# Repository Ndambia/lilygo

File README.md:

# LilyGo IoT Multi-Function PCB

A custom 4-layer KiCad PCB design integrating an ESP32 Wi-Fi/Bluetooth microcontroller with a SIM7600G-H 4G LTE Cat-4 cellular module, comprehensive power management, GPS tracking, GPRS connectivity, USB-C charging, LiPo battery management, environmental sensing, and USB-to-UART programming support.

---

## Table of Contents

- [Overview](#overview)
- [PCB Preview](#pcb-preview)
- [Schematic Overview](#schematic-overview)
- [Key Features](#key-features)
- [System Architecture](#system-architecture)
- [Schematic Sheets](#schematic-sheets)
- [Bill of Materials Summary](#bill-of-materials-summary)
- [Power System](#power-system)
- [Connectivity](#connectivity)
- [PCB Stackup & Design Rules](#pcb-stackup--design-rules)
- [Gerber & Manufacturing Files](#gerber--manufacturing-files)
- [Custom Libraries](#custom-libraries)
- [Datasheets](#datasheets)
- [Repository Structure](#repository-structure)
- [Getting Started](#getting-started)

---

## Overview

This project is a compact, feature-rich IoT development board built around the **ESP32-WROOM-32** and the **SIM7600G-H R2** 4G LTE module. It is designed for applications requiring cellular connectivity (4G/GPRS), GPS positioning, local Wi-Fi/Bluetooth, environmental sensing, and flexible power management from USB-C or a LiPo battery.

The board is designed in **KiCad** and targets JLCPCB / LCSC manufacturing and assembly (full BOM with LCSC part numbers included).

---

## PCB Preview

### Front Side (3D Render)

### Back Side (3D Render)

### PCB Layout (Top View)

---

## Schematic Overview

The full schematic (all sheets combined) is available as:

- 📄 [`PCB info/schematic.pdf`](PCB%20info/schematic.pdf) — Full combined schematic (all sheets)

Individual sheet PDFs:

| Sheet | Description | PDF |
|---|---|---|
| Root | Top-level schematic, ESP32, USB-UART, interfaces | *(see full schematic)* |
| BUCK\_CONVERTER\_3V3\_2A | 3.3 V / 2 A step-down (TPS56339DDCR) | [`schematic-BUCK_CONVERTER_3V3_2A_TPS56339DDCR.pdf`](PCB%20info/schematic-BUCK_CONVERTER_3V3_2A_TPS56339DDCR.pdf) |
| LIPO\_BAT\_CHARGER\_TP4056 | LiPo charger and protection circuit | [`schematic-LIPO_BAT_CHARGER_TP4056.pdf`](PCB%20info/schematic-LIPO_BAT_CHARGER_TP4056.pdf) |
| MT3608\_5V\_BOOST\_CONVERTOR | 5 V boost converter (MT3608) | [`schematic-MT3608_5V_BOOST_CONVERTOR.pdf`](PCB%20info/schematic-MT3608_5V_BOOST_CONVERTOR.pdf) |
| POWER\_PATH\_SELECTOR | Automatic USB/Battery power path switching | [`schematic-POWER_PATH_SELECTOR.pdf`](PCB%20info/schematic-POWER_PATH_SELECTOR.pdf) |
| SIM808\_GPRS\_GPS\_MODULE | SIM7600G-H R2 4G/GPS module and support circuitry | [`schematic-SIM808_GPRS_GPS_MODULE.pdf`](PCB%20info/schematic-SIM808_GPRS_GPS_MODULE.pdf) |

---

## Key Features

| Feature | Details |
|---|---|
| **MCU** | ESP32-WROOM-32D (Wi-Fi 802.11 b/g/n + Bluetooth 4.2 / BLE) |
| **Cellular** | SIM7600G-H R2 — 4G LTE Cat-4 / 3G / 2G, global bands |
| **GPS / GNSS** | Integrated via SIM7600G-H R2 (GPS + GLONASS) |
| **USB Interface** | USB-C receptacle (GCT USB4105), USB 2.0 |
| **USB-to-UART** | CH340T (SSOP-20) for ESP32 programming |
| **LiPo Charging** | TP4056 — up to 1 A charge rate, with protection |
| **3.3 V Rail** | TPS56339DDCR buck converter, 2 A output |
| **5 V Boost** | MT3608 step-up converter for 5 V peripherals |
| **Buck-Boost** | TPS630250RNCR — efficient intermediate rail |
| **Power Path** | Automatic USB / battery selector (NCE6005AR P-FETs) |
| **Environmental Sensor** | AM2302 (DHT22) — Temperature & Humidity |
| **PIR Sensor** | AS312 passive infrared motion detector |
| **SIM Card Slot** | GCT SIM7155-6-1-14-A nano/micro SIM connector |
| **GPS Antenna** | U.FL / IPEX connector (GT-RF1125A-01G) |
| **GPRS Antenna** | U.FL / IPEX connector (GT-RF1125A-01G) |
| **Level Shifting** | RS0108YQ20 8-channel bidirectional level shifter |
| **ESD Protection** | SP0502BAHT (USB lines), ESD0504F (multi-line) |
| **Reset / Boot** | Dedicated tactile push buttons (SKRPACE010) |
| **Status LEDs** | Power, Charging, Network status, RGB indicator |
| **Crystal** | 12 MHz SMD crystal (Y1) for CH340T |
| **PCB Layers** | 4-layer stackup (F.Cu / In1.Cu / In2.Cu / B.Cu) |
| **Board outline** | Edge cuts defined; antenna keep-out zone present |

---

## System Architecture

```
                          ┌──────────────────────────────────────────┐
                          │              USB-C (J3)                  │
                          │         GCT USB4105-GF-A                 │
                          └───────────────┬──────────────────────────┘
                                          │ VBUS (5V)
                          ┌───────────────▼──────────────────────────┐
                          │       Power Path Selector                │
                          │  NCE6005AR P-FET switches (Q8, Q9)       │
                          │  Auto USB / LiPo selection               │
                          └────────┬──────────────┬──────────────────┘
                                   │              │
                    ┌──────────────▼──┐    ┌──────▼──────────────────┐
                    │  TP4056 LiPo    │    │   MT3608 Boost (U2)     │
                    │  Charger (U4)   │    │   VBAT → 5 V            │
                    └──────────────┬──┘    └──────┬──────────────────┘
                                   │ VBAT         │ 5V rail
                    ┌──────────────▼──────────────▼──────────────────┐
                    │           TPS56339DDCR Buck (U10)              │
                    │              → 3.3 V / 2 A                     │
                    └──────────────┬──────────────────────────────────┘
                                   │ 3.3 V
                    ┌──────────────▼──────────────────────────────────┐
                    │         ESP32-WROOM-32D (U6)                   │
                    │    Wi-Fi / BLE / GPIO / UART / SPI / I2C       │
                    └──────┬──────────────┬──────────────────────────┘
                           │ UART         │ I2C / GPIO
          ┌────────────────▼──┐    ┌──────▼────────────────────────────┐
          │   CH340T (U8)     │    │   RS0108YQ20 Level Shifter (IC1)  │
          │   USB-UART Bridge │    │   3.3V ↔ 5V level translation     │
          └────────────────┬──┘    └──────┬────────────────────────────┘
                           │              │
                     USB-C (J3)    ┌──────▼──────────────────────────────┐
                  (programming)    │     SIM7600G-H R2 (IC4)             │
                                   │  4G LTE / 3G / 2G / GPS / GNSS     │
                                   │  GPS Antenna (AE4) + GPRS (AE3)    │
                                   │  SIM Card (J1 — SIM7155)           │
                                   └─────────────────────────────────────┘
                                   
          ┌────────────────────┐   ┌──────────────────┐
          │  AM2302 Sensor     │   │  AS312 PIR (IC2)  │
          │  Temp + Humidity   │   │  Motion Detection │
          └────────────────────┘   └──────────────────┘
```

---

## Schematic Sheets

The schematic is organized into hierarchical sheets:

### 1. Root Sheet
Top-level sheet containing:
- ESP32-WROOM-32D microcontroller and decoupling
- CH340T USB-to-UART bridge with 12 MHz crystal
- RS0108YQ20 bidirectional level shifter
- Reset and Boot buttons
- AM2302 temperature/humidity sensor
- AS312 PIR motion sensor
- Status LEDs (Power, Charging, Network, RGB)
- ESD protection diodes

### 2. BUCK_CONVERTER_3V3_2A_TPS56339DDCR
- Texas Instruments TPS56339DDCR synchronous buck regulator
- Input: up to ~5.5 V (battery or boosted USB)
- Output: 3.3 V @ 2 A for ESP32 and logic
- Teardrop-optimized copper pours

### 3. LIPO_BAT_CHARGER_TP4056
- TP4056 single-cell LiPo/Li-Ion charger IC
- Charge current configurable via R-prog resistor
- Charging indicator LED (D8 — Red) and Done indicator (D24 — Green)
- SS54 Schottky diode for reverse protection
- 4.2 V Zener clamp (D28) for overvoltage protection
- Large bulk capacitors (220 µF electrolytic on BAT+ rail)

### 4. MT3608_5V_BOOST_CONVERTOR
- MT3608 2 A boost converter (U2, SOT-23-6)
- Boosts VBAT (~3.7 V) to 5 V for USB and module power
- Inductor: 1 µH power bead (L2)
- SS54 freewheeling diode

### 5. POWER_PATH_SELECTOR
- Automatic switchover between USB VBUS and LiPo battery
- P-channel MOSFETs NCE6005AR (Q8, Q9) in back-to-back configuration
- Prevents battery discharge when USB is connected
- Handles reverse current blocking

### 6. SIM808_GPRS_GPS_MODULE (SIM7600G-H R2)
- SIM7600G-H R2 global-band 4G LTE Cat-4 module (IC4)
- GPS/GLONASS integrated receiver
- GPRS antenna connector AE3 (U.FL / IPEX)
- GPS antenna connector AE4 (U.FL / IPEX)
- SIM card connector J1 (GCT SIM7155-6-1-14-A)
- TPS630250RNCR buck-boost for module power rail
- Large 220 µF tantalum bulk capacitors for surge current

---

## Bill of Materials Summary

> Full BOM: [`Manufacturing files/BOM.csv`](Manufacturing%20files/BOM.csv)  
> Schematic netlist CSV: [`schematic.csv`](schematic.csv)

### ICs & Modules

| Ref | Part | Description |
|---|---|---|
| U6 | ESP32-WROOM-32D-N4 | Wi-Fi + BT MCU module |
| IC4 | SIM7600G-H R2 | 4G LTE / GPS module |
| U4 | TP4056 | LiPo battery charger |
| U10 | TPS56339DDCR | 3.3 V / 2 A buck regulator |
| U2 | MT3608 | 5 V boost converter |
| IC3 | TPS630250RNCR | Buck-boost regulator |
| IC1 | RS0108YQ20 | 8-ch bidirectional level shifter |
| IC2 | AS312 | PIR motion sensor |
| U8 | CH340T (SSOP-20) | USB-to-UART bridge |
| U3 | AM2302 | DHT22 temperature & humidity sensor |

### Connectors

| Ref | Part | Description |
|---|---|---|
| J3 | USB4105-GF-A | USB-C receptacle (USB 2.0) |
| J1 | SIM7155-6-1-14-A | SIM card connector |
| AE3 | GT-RF1125A-01G | GPRS / LTE antenna (U.FL) |
| AE4 | GT-RF1125A-01G | GPS antenna (U.FL) |

### Semiconductors & Passives (Key)

| Ref | Value/Part | Description |
|---|---|---|
| Q8, Q9 | NCE6005AR | P-channel power MOSFETs (power path) |
| Q15, Q16 | SI2302 | N-channel MOSFETs |
| Q10, Q11 | MMBT3904 | NPN signal transistors |
| Q1 | BC817 | NPN transistor |
| D1, D17 | SS54 | 5 A Schottky diodes |
| D10–D12 | B5819W | 1 A Schottky diodes |
| D13 | BAT54C | Dual Schottky (SOT-23) |
| D28 | BZT52C4V3 | 4.3 V Zener clamp |
| D3 | SMLVN6RGBFU1 | RGB LED |
| D15, D16 | SP0502BAHT | USB ESD protection |
| D25 | ESD0504F | Multi-line ESD protection |
| Y1 | 12 MHz | SMD crystal (2520 4-pin) for CH340T |
| L1 | 22 µH | Chilisin power inductor (buck) |
| L2 | 1 µH | Chilisin power inductor (boost) |
| L5 | 4.7 µH | Chilisin power inductor (buck-boost) |
| C31, C35 | 220 µF | Electrolytic bulk caps |
| C23, C67 | 220 µF | Tantalum bulk caps (cellular surge) |

Total unique component lines in BOM: **~82 line items**

---

## Power System

```
USB-C VBUS (5 V)
     │
     ├──► Power Path Selector (NCE6005AR)
     │         │
     │    ┌────┴──────────────────────────────────────────┐
     │    │ When USB present: powers system, charges LiPo │
     │    │ When no USB: LiPo powers system               │
     │    └────────────────────────────────────────────────┘
     │
     ├──► TP4056 LiPo Charger ──► LiPo Battery (BAT+ / BAT-)
     │
     └──► MT3608 Boost ──► 5 V internal rail
               │
               └──► TPS56339DDCR Buck ──► 3.3 V (ESP32, logic, peripherals)
                         │
                         └──► TPS630250RNCR Buck-Boost ──► SIM7600G-H power rail
```

| Rail | Regulator | Max Current | Load |
|---|---|---|---|
| 5 V boost | MT3608 | 2 A | Module VCC, USB |
| 3.3 V | TPS56339DDCR | 2 A | ESP32, logic ICs, sensors |
| Module VCC | TPS630250RNCR | — | SIM7600G-H R2 |
| VBAT | TP4056 output | 1 A charge | LiPo cell |

---

## Connectivity

| Interface | Notes |
|---|---|
| **4G LTE / GPRS** | SIM7600G-H R2, global bands, SMA/U.FL antenna |
| **GPS / GNSS** | Integrated in SIM7600G-H R2, dedicated U.FL antenna |
| **Wi-Fi** | ESP32 802.11 b/g/n (PCB trace antenna on module) |
| **Bluetooth** | ESP32 BT Classic 4.2 + BLE |
| **USB** | USB-C, USB 2.0, via CH340T UART bridge for programming |
| **Temperature/Humidity** | AM2302 (DHT22) single-wire protocol |
| **PIR Motion** | AS312 digital output |
| **SIM** | Nano/micro SIM via GCT connector |

---

## PCB Stackup & Design Rules

| Parameter | Value |
|---|---|
| **Layers** | 4 (F.Cu, In1.Cu, In2.Cu, B.Cu) |
| **Min track width** | 0.2 mm |
| **Min clearance** | 0.129 mm |
| **Min via diameter** | 0.6 mm |
| **Via drill** | 0.3 mm |
| **Min annular ring** | 0.15 mm |
| **Min hole-to-hole** | 0.25 mm |
| **Min copper-edge clearance** | 0.5 mm |
| **Solder mask clearance** | 0.005 mm |
| **Track widths used** | 0.19, 0.25, 0.3, 0.6 mm |
| **Teardrops** | Enabled on PTH pads, SMD pads, and vias |

> ⚠️ **Antenna Keep-Out Zone**: A copper-free keep-out zone is defined above the ESP32 module and near the cellular/GPS antenna connectors. Do not route traces or place copper fills in this area.

---

## Gerber & Manufacturing Files

### Gerber Files (`Gerber/`)

| File | Layer |
|---|---|
| `schematic-F_Cu.gbr` | Front copper |
| `schematic-B_Cu.gbr` | Back copper |
| `schematic-In1_Cu.gbr` | Inner layer 1 |
| `schematic-In2_Cu.gbr` | Inner layer 2 |
| `schematic-F_Mask.gbr` | Front solder mask |
| `schematic-B_Mask.gbr` | Back solder mask |
| `schematic-F_Paste.gbr` | Front solder paste |
| `schematic-B_Paste.gbr` | Back solder paste |
| `schematic-F_Silkscreen.gbr` | Front silkscreen |
| `schematic-B_Silkscreen.gbr` | Back silkscreen |
| `schematic-Edge_Cuts.gbr` | Board outline |
| `schematic-PTH.drl` | Plated through-hole drill file |
| `schematic-NPTH.drl` | Non-plated through-hole drill file |
| `schematic-job.gbrjob` | Gerber job file |

> 📦 Pre-zipped package: [`Gerber.zip`](Gerber.zip)

### Manufacturing Files (`Manufacturing files/`)

| File | Description |
|---|---|
| [`BOM.csv`](Manufacturing%20files/BOM.csv) | Full BOM with LCSC part numbers for JLCPCB SMT |
| [`Gerber.zip`](Manufacturing%20files/Gerber.zip) | Gerber archive for board fabrication |
| `placement/schematic-all-pos.csv` | Component placement / pick-and-place file |

---

## Custom Libraries (`lib/`)

Custom KiCad footprint and symbol libraries used in this project:

| Library | Part |
|---|---|
| `LIB_AM2302` | DHT22 / AM2302 temperature & humidity sensor |
| `LIB_AS312` | AS312 PIR motion sensor |
| `LIB_AXP2101` | AXP2101 power management IC |
| `LIB_RS0108YQ20` | RS0108YQ20 level shifter |
| `LIB_SIM7080G` | SIM7080G NB-IoT / Cat-M module |
| `LIB_SIM7600G-H_R2` | SIM7600G-H R2 4G module |
| `LIB_SKRPACE010` | SKRPACE010 tactile switch |
| `LIB_TP4056` | TP4056 LiPo charger |
| `LIB_TPS630250RNCR` | TPS630250RNCR buck-boost regulator |
| `Antenna conector` | U.FL / IPEX antenna connector |
| `SIM7155_6_1_14_A` | GCT SIM card connector |

---

## Datasheets (`Datasheet/`)

| Document | Description |
|---|---|
| [`AXP2101.pdf`](Datasheet/AXP2101.pdf) | AXP2101 PMIC datasheet |
| [`T-SIM7080G_Schematic.pdf`](Datasheet/T-SIM7080G_Schematic.pdf) | LilyGo T-SIM7080G reference schematic |
| [`TDM-2202_TDM-2205_ESP32-X7600X_schematic.pdf`](Datasheet/TDM-2202_TDM-2205_ESP32-X7600X_schematic.pdf) | ESP32 + SIM7600 reference design |
| [`sim7600 schematic.pdf`](Datasheet/sim7600%20schematic.pdf) | SIM7600 series module schematic reference |
| [`tps630250.pdf`](Datasheet/tps630250.pdf) | TPS630250 buck-boost regulator datasheet |

---

## Repository Structure

```
lilygo/
├── README.md                    ← This file
├── schematic.csv                ← Component netlist export
├── Gerber.zip                   ← Fabrication-ready Gerber archive
│
├── PCB info/                    ← Visual references
│   ├── Front 3d.jpg             ← 3D render — front
│   ├── back 3d.jpg              ← 3D render — back
│   ├── Shem 1.jpg               ← PCB layout screenshot
│   ├── schematic.pdf            ← Full combined schematic PDF
│   ├── schematic-BUCK_CONVERTER_3V3_2A_TPS56339DDCR.pdf
│   ├── schematic-LIPO_BAT_CHARGER_TP4056.pdf
│   ├── schematic-MT3608_5V_BOOST_CONVERTOR.pdf
│   ├── schematic-POWER_PATH_SELECTOR.pdf
│   └── schematic-SIM808_GPRS_GPS_MODULE.pdf
│
├── schematic/                   ← KiCad project files
│   ├── schematic.kicad_pro      ← KiCad project settings
│   ├── schematic.kicad_pcb      ← PCB layout file
│   ├── schematic.kicad_sch      ← Root schematic sheet
│   ├── BUCK_CONVERTER_3V3_2A_TPS56339DDCR.kicad_sch
│   ├── LIPO_BAT_CHARGER_TP4056.kicad_sch
│   ├── MT3608_5V_BOOST_CONVERTOR.kicad_sch
│   ├── POWER_PATH_SELECTOR.kicad_sch
│   └── SIM808_GPRS_GPSS_MODULE.kicad_sch
│
├── Gerber/                      ← Individual Gerber layer files
├── Manufacturing files/         ← JLCPCB production package
│   ├── BOM.csv                  ← BOM with LCSC part numbers
│   ├── Gerber.zip
│   └── placement/
│       └── schematic-all-pos.csv ← Pick-and-place file
│
├── lib/                         ← Custom KiCad libraries
│   ├── LIB_AM2302/
│   ├── LIB_AS312/
│   ├── LIB_SIM7600G-H_R2/
│   ├── LIB_TP4056/
│   ├── LIB_TPS630250RNCR/
│   └── ...
│
├── Datasheet/                   ← Reference datasheets
└── placement/                   ← Placement CSV (root-level copy)
```

---

## Getting Started

### Prerequisites

- [KiCad 7 or later](https://www.kicad.org/download/) (project was created with KiCad 7/8)
- LCSC / JLCPCB account for ordering

### Opening the Project

1. Clone or download this repository.
2. Open KiCad and select **File → Open Project**.
3. Navigate to `schematic/schematic.kicad_pro` and open it.
4. The schematic editor and PCB layout editor will be available from the KiCad project manager.

> **Note**: Ensure the `lib/` directory is accessible to KiCad for custom footprints and symbols. If prompted, add `lib/` as a project-level footprint library path in **Preferences → Manage Footprint Libraries**.

### Ordering the PCB (JLCPCB)

1. Upload [`Gerber.zip`](Gerber.zip) (or [`Manufacturing files/Gerber.zip`](Manufacturing%20files/Gerber.zip)) to [JLCPCB](https://jlcpcb.com).
2. Select **4-layer** stackup.
3. For SMT assembly, also upload:
   - [`Manufacturing files/BOM.csv`](Manufacturing%20files/BOM.csv)
   - [`Manufacturing files/placement/schematic-all-pos.csv`](Manufacturing%20files/placement/schematic-all-pos.csv)
4. Review component availability and substitutions as needed.

### Programming the ESP32

The board includes an on-board CH340T USB-to-UART bridge. To program:

1. Connect a USB-C cable to **J3**.
2. The CH340T will enumerate as a serial COM port.
3. Use the Arduino IDE, ESP-IDF, or PlatformIO targeting **ESP32-WROOM-32**.
4. Hold **BOOT** button while pressing **RESET** to enter download mode if needed.

---

*PCB designed in KiCad. Manufactured via JLCPCB. All LCSC part numbers included in BOM for one-stop sourcing.*

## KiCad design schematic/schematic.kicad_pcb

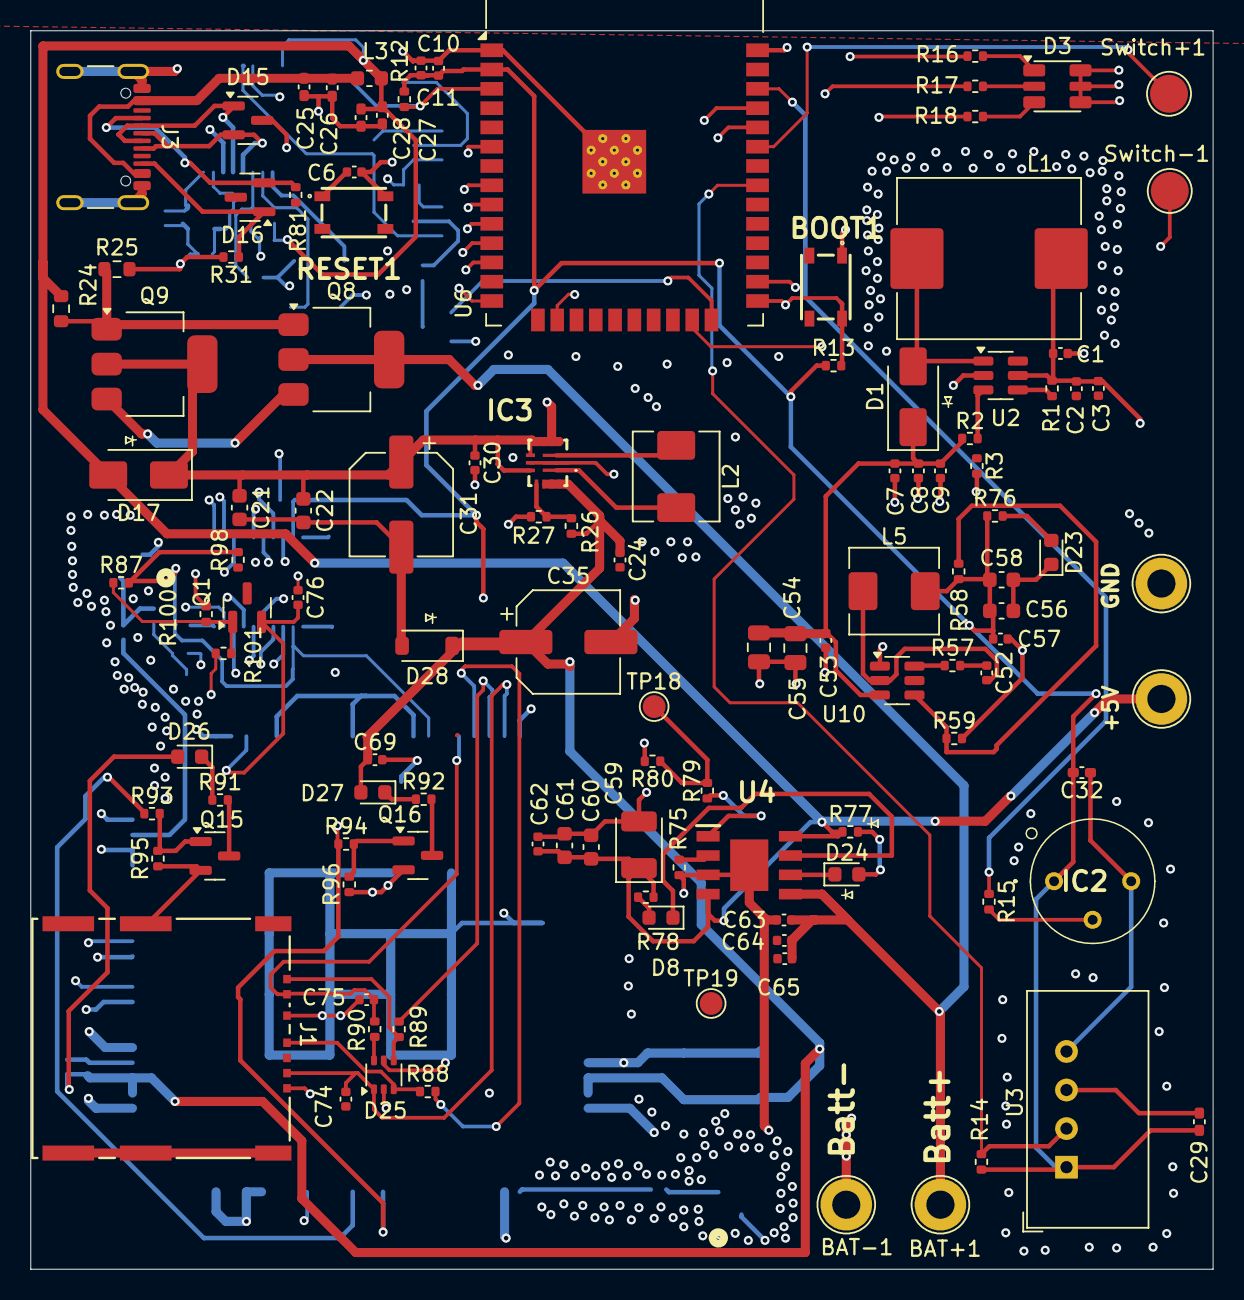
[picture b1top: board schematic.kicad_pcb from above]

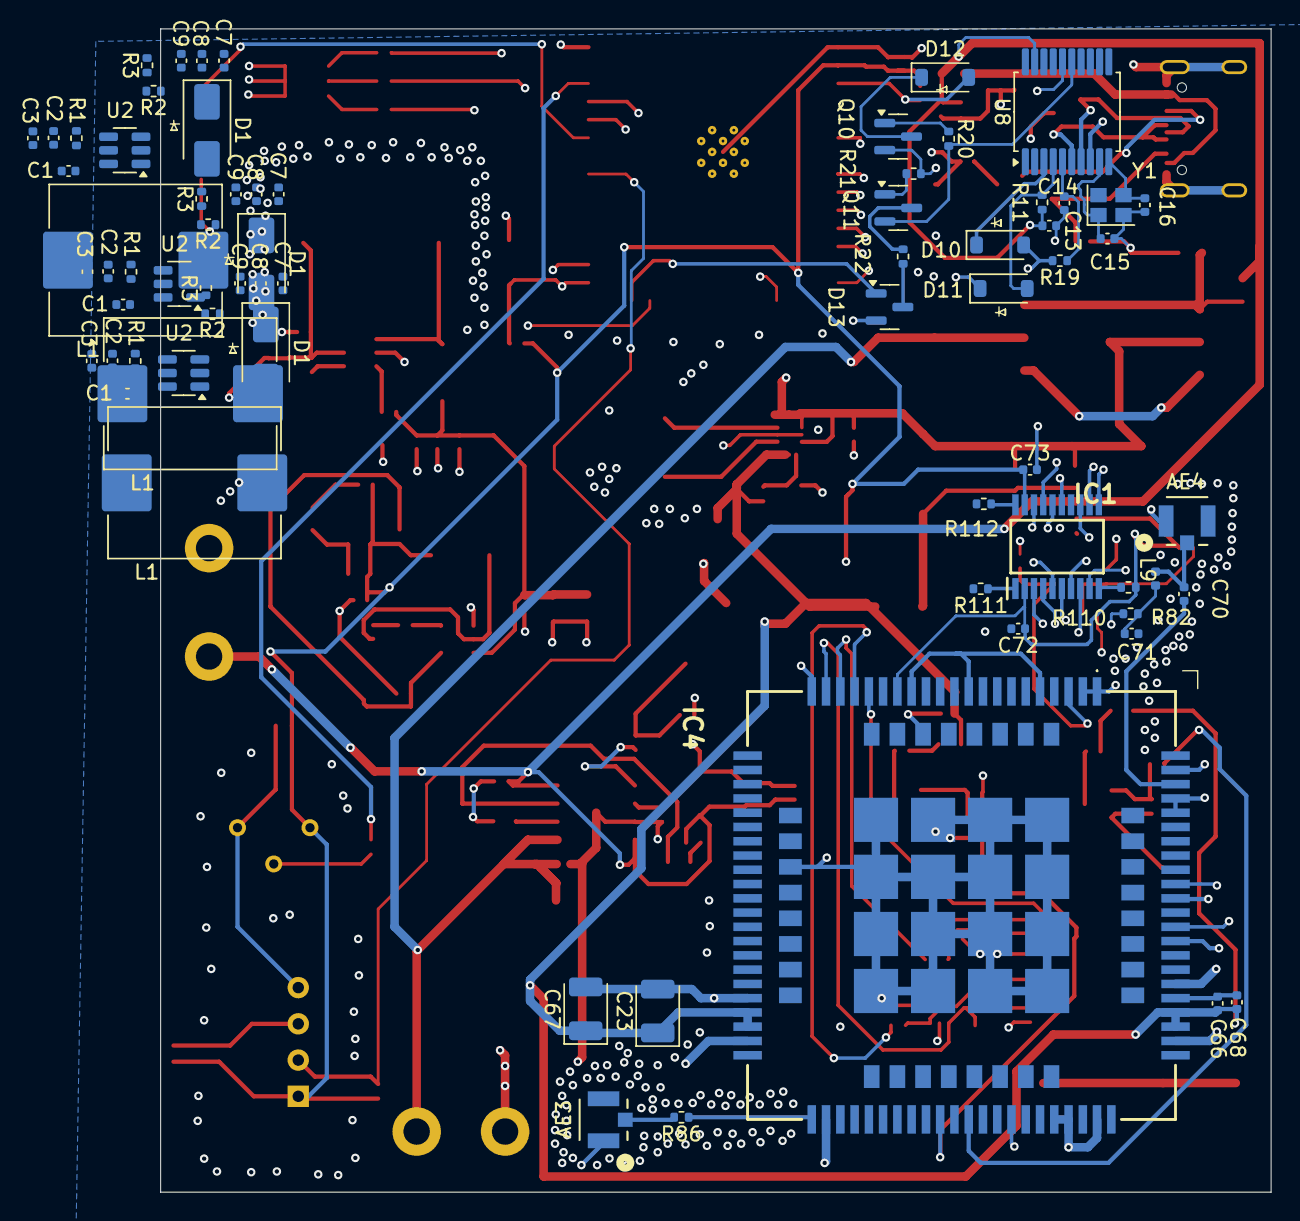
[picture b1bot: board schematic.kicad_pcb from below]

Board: 4 copper layers, 77.8 x 81.6 mm, 188 parts (71 on the bottom side), 98 nets.

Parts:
+5V: 5v; TestPoint_Loop_D2.50mm_Drill1.85mm
AE3: GPRS_ANTENNA; CONN_2337019-1_TEC
AE4: GPS_ANTENNA; CONN_2337019-1_TEC
BAT+1: BAT+; TestPoint_Loop_D2.50mm_Drill1.85mm
BAT-1: BAT-; TestPoint_Loop_D2.50mm_Drill1.85mm
BOOT1: SW_Push; SMT_4.2X3.2_
C1, C1#2, C1#3, C1#4, C2, C2#2, C2#3, C2#4, C8, C8#2, C8#3, C8#4, C9, C9#2, C9#3, C9#4, C30, C64, C65: 22u; C_0402_1005Metric
C3, C3#2, C3#3, C3#4, C7, C7#2, C7#3, C7#4, C24, C62, C63, C66, C72, C73, C74, C76: 100n; C_0402_1005Metric
C6, C11: 0.1u; C_0402_1005Metric
C10, C68: 10u; C_0402_1005Metric
C13: 22uF; C_0402_1005Metric
C14, C52: 100nF; C_0402_1005Metric
C15, C16: 22pF; C_0402_1005Metric
C21: 4.7u; C_0603_1608Metric
C22, C60: 10u; C_0603_1608Metric
C23, C67: 220u; CP_EIA-3528-21_Kemet-B
C25, C28: 4.7u; C_0402_1005Metric_Pad0.74x0.62mm_HandSolder
C26: 10n; C_0402_1005Metric_Pad0.74x0.62mm_HandSolder
C27, C29, C32: 100n; C_0402_1005Metric_Pad0.74x0.62mm_HandSolder
C31, C35: 220u; CP_Elec_6.3x5.4
C53, C57: 100nF_65V; C_0402_1005Metric
C54, C55: 10uF; C_0805_2012Metric
C56, C58: 22uF; C_0603_1608Metric
C59: 47u; CP_EIA-3528-21_Kemet-B
C61: 100n; C_0603_1608Metric
C69, C71: 33p; C_0402_1005Metric
C70, C75: 22p; C_0402_1005Metric
D1, D1#2, D1#3, D1#4, D17: SS54; D_SMA
D3: SMLVN6RGB; LED_ROHM_SMLVN6
D8: CHARGING_RED_LED; LED_0603_1608Metric
D10, D11, D12: B5819W; D_SOD-123
D13: BAT54C; SOT-23
D15, D16: SP0502BAHT; SOT-23
D23: PWR; LED_0603_1608Metric
D24: DONE_GRN_LED; LED_0603_1608Metric
D25: ESD0504F; SOT-363_SC-70-6
D26: LED_net; LED_0603_1608Metric
D27: LED_status; LED_0603_1608Metric
D28: 4.2v Zener; D_SOD-123
GND: GND; TestPoint_Loop_D2.50mm_Drill1.85mm
IC1: RS0108YQ20; SOP65P640X120-20N
IC2: AS312
IC3: TPS630250RNCR
IC4: SIM7600G-H_R2; SIM7600GHR2
J1: SIM7155-6-1-14-A; SIM7155-6-1-14-A_GCT
J3: USB_C_Receptacle_USB2.0; USB_C_Receptacle_GCT_USB4105-xx-A_16P_TopMnt_Horizontal
L1, L1#2, L1#3, L1#4: 22uH; L_Chilisin_BMRG00101030
L2: 1uH; L_Chilisin_BMRx00050512-B
L3: 2A_bead; L_0603_1608Metric
L5: 4.7uH; L_Chilisin_BMRx00050512-B
L9: 47nH; L_0402_1005Metric
Q1: BC817; SOT-23
Q8, Q9: NCE6005AR; SOT-223-3_TabPin2
Q10, Q11: MMBT3904; SOT-23
Q15, Q16: SI2302; SOT-23
R1, R1#2, R1#3, R1#4, R59, R95, R96: 10K; R_0402_1005Metric
R2, R2#2, R2#3, R2#4: 120K; R_0402_1005Metric
R3, R3#2, R3#3, R3#4: 16K; R_0402_1005Metric
R11, R12, R13, R19, R20, R21, R110: 10k; R_0402_1005Metric
R14, R87, R98, R100, R101: 4.7k; R_0402_1005Metric
R15, R16, R17, R18: 1k; R_0402_1005Metric
R22: 220R; R_0402_1005Metric
R24: 1K; R_0603_1608Metric
R25: 10K; R_0603_1608Metric
R26: 720K; R_0402_1005Metric
R27: 180K; R_0402_1005Metric
R31, R81: 5.1K; R_0402_1005Metric
R57: 30R; R_0402_1005Metric
R58: 30.9K; R_0402_1005Metric
R75, R76, R77, R78, R93, R94: 1K; R_0402_1005Metric
R79: 4870; R_0402_1005Metric
R80: 86600; R_0402_1005Metric
R82: 47R; R_0402_1005Metric
R86: 0R; R_0402_1005Metric
R88, R89, R90: 22R; R_0402_1005Metric
R91, R92: 390R; R_0402_1005Metric
R111, R112: 47k; R_0402_1005Metric
RESET1: SW_Push; SMT_4.2X3.2_
Switch+1: Switch+; TestPoint_Pad_D2.5mm
Switch-1: Switch-; TestPoint_Pad_D2.5mm
TP18: THERM+; TestPoint_Pad_D1.5mm
TP19: THERM-; TestPoint_Pad_D1.5mm
U2, U2#2, U2#3, U2#4: MT3608; SOT-23-6
U3: AM2302; ASAIR_AM2302_P2.54mm_Vertical
U4: TP4056; SOIC127P600X175-9N
U6: ESP32-WROOM-32
U8: CH340T(SSOP20W); SSOP-20_5.3x7.2mm_P0.65mm
U10: TPS56339DDC; SOT-23-6
Y1: 12MHz; Crystal_SMD_2520-4Pin_2.5x2.0mm

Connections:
4.2v: C23.1, C24.1, C35.1, C66.1, C67.1, C68.1, C69.1, D26.2 (A), D27.2 (A), D28.1 (K), IC3.12 (VOUT_1), IC3.13 (VOUT_2), IC3.14 (VOUT_3), IC4.38 (VBAT_1), IC4.39 (VBAT_2), IC4.62 (VBAT_3), IC4.63 (VBAT_4), R26.1
+3V3: C10.1, C11.1, C29.2, C32.2, C56.1, C57.1, C58.1, C73.1, IC1.19 (VCCB), IC2.1 (VDD), L5.2, R12.1, R13.1, R14.1, R58.1, R76.1, R82.1, U3.1 (VDD), U6.2 (VDD)
+5V: +5V.1, C13.1, C27.1, C28.1, C59.1, C60.1, C61.1, C62.1, D17.2 (A), L3.1, R11.1, R24.1, R77.1, R78.1, U4.4 (VCC), U4.8 (CE), U8.19 (VCC)
+BATT: BAT+1.1, C63.1, C64.1, C65.1, Q8.2 (D), U4.5 (BAT)
/D+: D15.2 (K), J3.A6 (D+), J3.B6 (D+), U8.6 (UD+)
/D-: D15.1 (K), J3.A7 (D-), J3.B7 (D-), U8.7 (UD-)
/DHT22_Data: R14.2, U3.2 (SDA), U6.31 (IO19)
/IO2: D13.1, U6.24 (IO2)
/MT3608_1.2mHz_STEP-UP_CONVERTOR/power_input: C1.1, C1#2.1, C1#3.1, C1#4.1, C2.1, C2#2.1, C2#3.1, C2#4.1, C3.1, C3#2.1, C3#3.1, C3#4.1, C21.1, C22.1, C30.1, C31.1, D17.1 (K), IC3.4 (VIN_1), IC3.5 (VIN_2), IC3.6 (VIN_3), IC3.7 (VINA), IC3.8 (EN), IC3.10 (PFM/PWM), L1.1, L1#2.1, L1#3.1, L1#4.1, Q9.2 (D), R1.2, R1#2.2, R1#3.2, R1#4.2, U2.5 (IN), U2#2.5 (IN), U2#3.5 (IN), U2#4.5 (IN)
/MT3608_5V_BOOST_CONVERTOR/5v: C7.1, C7#2.1, C7#3.1, C7#4.1, C8.1, C8#2.1, C8#3.1, C8#4.1, C9.1, C9#2.1, C9#3.1, C9#4.1, C53.1, C54.1, C55.1, D1.1 (K), D1#2.1 (K), D1#3.1 (K), D1#4.1 (K), R2.1, R2#2.1, R2#3.1, R2#4.1, U10.3 (VIN)
/Motion_out: R15.1, U6.36 (IO22)
/SIM808_GPRS_GPS_MODULE/1.8v_OUT: C72.1, IC1.2 (VCCA), IC4.15 (VDD_1V8), R87.2, R98.2, R110.1
/SIM808_GPRS_GPS_MODULE/DTR: IC1.6 (A5), IC4.72 (DTR)
/SIM808_GPRS_GPS_MODULE/Flight: IC1.5 (A4), IC4.54 (FLIGHTMODE)
/SIM808_GPRS_GPS_MODULE/LED_Netlight: IC4.51 (NETLIGHT), R93.1
/SIM808_GPRS_GPS_MODULE/LED_Status: IC1.7 (A6), IC4.49 (STATUS), R94.1
/SIM808_GPRS_GPS_MODULE/RI: IC1.8 (A7), IC4.69 (RI)
/SIM808_GPRS_GPS_MODULE/SIM7600_RXD: IC1.4 (A3), IC4.68 (RXD)
/SIM808_GPRS_GPS_MODULE/SIM7600_TXD: IC1.3 (A2), IC4.71 (TXD)
/SIM808_GPRS_GPS_MODULE/SIM_CLK: IC4.19 (USIM_CLK), R89.2
/SIM808_GPRS_GPS_MODULE/SIM_DATA: C75.1, IC4.17 (USIM_DATA), J1.C7 (I/O), R90.2
/SIM808_GPRS_GPS_MODULE/SIM_RST: IC4.18 (USIM_RST), R88.2
/SIM808_GPRS_GPS_MODULE/SIM_VDD: C74.1, D25.1 (TVS1), IC4.20 (USIM_VDD), J1.C1 (VCC)
/SIM808_GPRS_GPS_MODULE/pwrkey: C76.2, IC4.3 (PWRKEY), Q1.2 (E)
/blue: R16.1, U6.23 (IO15)
/boot: BOOT1.2, D13.2, R13.2, U6.25 (IO0)
/dtr: Q10.2 (E), R21.2, U8.16 (RTS#)
/green: R18.1, U6.16 (IO13)
/red: R17.1, U6.14 (IO12)
/switch: Switch+1.1, U6.33 (IO21)
/~esp_rst: C6.1, D12.2 (A), R12.2, RESET1.2, U6.3 (EN)
ESP_RX: D10.2 (A), R19.2, U6.34 (RXD0/IO3)
ESP_TX: D11.1 (K), U6.35 (TXD0/IO1)
GND: AE3.2 (Shield), AE4.2 (Shield), BAT-1.1, BOOT1.1, C1.2, C1#2.2, C1#3.2, C1#4.2, C2.2, C2#2.2, C2#3.2, C2#4.2, C3.2, C3#2.2, C3#3.2, C3#4.2, C6.2, C7.2, C7#2.2, C7#3.2, C7#4.2, C8.2, C8#2.2, C8#3.2, C8#4.2, C9.2, C9#2.2, C9#3.2, C9#4.2, C10.2, C11.2, C13.2, C14.2, C15.2, C16.2, C21.2, C22.2, C23.2, C24.2, C25.2, C26.2, C27.2, C28.2, C29.1, C30.2, C31.2, C32.1, C35.2, C53.2, C54.2, C55.2, C56.2, C57.2, C58.2, C59.2, C60.2, C61.2, C62.2, C63.2, C64.2, C65.2, C66.2, C67.2, C68.2, C69.2, C71.2, C72.2, C73.2, C74.2, C75.2, C76.1, D3.4 (GK), D3.5 (RK), D3.6 (BK), D15.3 (A), D16.3 (A), D23.1 (K), D25.2 (COM), D25.5 (COM), D28.2 (A), GND.1, IC1.9 (A8), IC1.11 (GND), IC1.12 (B8), IC2.3 (VSS), IC3.2 (PGND), IC3.9 (GND), IC4.1 (GND_1), IC4.2 (GND_2), IC4.37 (GND_6), IC4.40 (GND_7), IC4.41 (GND_8), IC4.43 (GND_9), IC4.57 (GND_10), IC4.58 (GND_11), IC4.60 (GND_12), IC4.61 (GND_13), IC4.64 (GND_14), IC4.65 (GND_15), IC4.77 (GND_16), IC4.78 (GND_17), IC4.80 (GND_18), IC4.81 (GND_19), IC4.93 (GND_20), IC4.98 (GND_21), IC4.110 (GND_22), IC4.118 (GND_23), IC4.120 (GND_24), IC4.121 (GND_25), IC4.122 (GND_26), IC4.123 (GND_27), IC4.124 (GND_28), IC4.125 (GND_29), IC4.126 (GND_30), IC4.127 (GND_31), IC4.128 (GND_32), IC4.129 (GND_33), IC4.130 (GND_34), IC4.131 (GND_35), IC4.132 (GND_36), IC4.133 (GND_37), IC4.134 (GND_38), IC4.135 (GND_39), J1.C5 (GND), J1.CD, J1.GND1, J1.GND2, J1.GND3, J1.GND4, J1.GND5, J1.GND6, J3.A1 (GND), J3.A12 (GND), J3.B1 (GND), J3.B12 (GND), J3.S1 (SHIELD), Q1.3 (C), Q15.2 (S), Q16.2 (S), R3.2, R3#2.2, R3#3.2, R3#4.2, R25.2, R27.2, R31.2, R59.2, R75.2, R80.2, R81.2, R95.1, R96.1, R101.1, R111.2, R112.2, RESET1.1, Switch-1.1, TP19.1, U2.2 (GND), U2#2.2 (GND), U2#3.2 (GND), U2#4.2 (GND), U3.3 (GND), U3.4 (GND), U4.3 (GND), U4.9 (EP), U6.1 (GND), U6.15 (GND), U6.38 (GND), U6.39 (GND), U8.8 (GND), U10.1 (GND), Y1.2
IO4: R100.2, U6.26 (IO4)
IO25: IC1.16 (B4), U6.10 (IO25)
IO26: IC1.18 (B2), U6.11 (IO26)
IO27: IC1.17 (B3), U6.12 (IO27)
IO32: IC1.15 (B5), U6.8 (IO32)
IO33: IC1.13 (B7), U6.9 (IO33)
IO34: IC1.14 (B6), U6.6 (IO34)
unnamed: AE3.1 (A), R86.2
unnamed: AE4.1 (A), C70.2, L9.2
unnamed: C52.1, R57.2
unnamed: C71.1, L9.1, R82.2
unnamed: D1.2 (A), D1#2.2 (A), D1#3.2 (A), D1#4.2 (A), L1.2, L1#2.2, L1#3.2, L1#4.2, U2.1 (SW), U2#2.1 (SW), U2#3.1 (SW), U2#4.1 (SW)
unnamed: D3.1 (BA), R16.2
unnamed: D3.3 (GA), R18.2
unnamed: D3.2 (RA), R17.2
unnamed: D8.2 (A), R78.2
unnamed: D8.1 (K), U4.7 (~CHRG)
unnamed: D10.1 (K), U8.3 (TXD)
unnamed: D11.2 (A), R11.2, U8.4 (RXD)
unnamed: D12.1 (K), Q10.3 (C)
unnamed: D13.3, R22.1
unnamed: D23.2 (A), R76.2
unnamed: D24.2 (A), R77.2
unnamed: D24.1 (K), U4.6 (~STDBY)
unnamed: D25.3 (TVS2), J1.C2 (RST), R88.1
unnamed: D25.4 (TVS3), J1.C3 (CLK), R89.1
unnamed: D25.6 (TVS4), R90.1
unnamed: D26.1 (K), R91.1
unnamed: D27.1 (K), R92.1
unnamed: IC1.1 (A1), R111.1
unnamed: IC1.20 (B1), R112.1
unnamed: IC1.10 (OE), R110.2
unnamed: IC2.2 (REL), R15.2
unnamed: IC3.11 (FB), R26.2, R27.1
unnamed: IC3.3 (L1), L2.1
unnamed: IC3.1 (L2), L2.2
unnamed: IC4.5 (GND_3), IC4.10 (GND_4), IC4.14 (GND_5)
unnamed: C70.1, IC4.79 (GNSS_ANT)
unnamed: IC4.82 (MAIN_ANT), R86.1
unnamed: D16.2 (K), J3.A5 (CC1), R81.1
unnamed: D16.1 (K), J3.B5 (CC2), R31.1
unnamed: Q1.1 (B), R87.1, R100.1, R101.2
unnamed: Q8.1 (G), Q9.1 (G), R24.2, R25.1
unnamed: Q8.3 (S), Q9.3 (S)
unnamed: Q10.1 (B), R20.1
unnamed: Q11.1 (B), R21.1
unnamed: Q11.3 (C), R22.2
unnamed: Q11.2 (E), R20.2, U8.15 (DTR#)
unnamed: Q15.3 (D), R91.2
unnamed: Q15.1 (G), R93.2, R95.2
unnamed: Q16.3 (D), R92.2
unnamed: Q16.1 (G), R94.2, R96.2
unnamed: R79.2, R80.1, TP18.1
unnamed: R1.1, R1#2.1, R1#3.1, R1#4.1, U2.4 (EN), U2#2.4 (EN), U2#3.4 (EN), U2#4.4 (EN)
unnamed: R2.2, R2#2.2, R2#3.2, R2#4.2, R3.1, R3#2.1, R3#3.1, R3#4.1, U2.3 (FB), U2#2.3 (FB), U2#3.3 (FB), U2#4.3 (FB)
unnamed: R75.1, U4.2 (PROG)
unnamed: R79.1, U4.1 (TEMP)
unnamed: C14.1, R19.1, U8.5 (V3)
unnamed: C15.1, U8.9 (XI), Y1.1
unnamed: C16.1, U8.10 (XO), Y1.3
unnamed: R57.1, U10.6 (BOOT)
unnamed: R58.2, R59.1, U10.4 (FB)
unnamed: C52.2, L5.1, U10.2 (SW)
VBUS: C25.1, C26.1, J3.A4 (VBUS), J3.A9 (VBUS), J3.B4 (VBUS), J3.B9 (VBUS), L3.2

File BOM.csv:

"Id";"Designator";"Footprint";"Quantity";"Designation";"Supplier and ref";
1;"U1";"ESP32-S3-WROOM-1";1;"ESP32-S3-WROOM-1";;;
2;"J1";"SIM7155-6-1-14-A_GCT";1;"SIM7155-6-1-14-A";;;
3;"Switch-1";"TestPoint_Pad_D2.5mm";1;"Switch-";;;
4;"Switch+1";"TestPoint_Pad_D2.5mm";1;"Switch+";;;
5;"R18,R17,R16,R15";"R_0402_1005Metric";4;"1k";;;
6;"D3";"LED_ROHM_SMLVN6";1;"SMLVN6RGB";;;
7;"Q1,Q2";"SOT-23";2;"BC817";;;
8;"R78,R75,R77,R94,R76,R93";"R_0402_1005Metric";6;"1K";;;
9;"C63,C62,C24,C74,C3,C7,C66";"C_0402_1005Metric";7;"100n";;;
10;"R80";"R_0402_1005Metric";1;"86600";;;
11;"R79";"R_0402_1005Metric";1;"4870";;;
12;"D24";"LED_0603_1608Metric";1;"DONE_GRN_LED";;;
13;"C60,C22";"C_0603_1608Metric";2;"10u";;;
14;"C59";"CP_EIA-3528-21_Kemet-B";1;"47u";;;
15;"D8";"LED_0603_1608Metric";1;"CHARGING_RED_LED";;;
16;"U4";"SOIC127P600X175-9N";1;"TP4056";;;
17;"C64,C65,C9,C8,C1,C2,C30";"C_0402_1005Metric";7;"22u";;;
18;"C61";"C_0603_1608Metric";1;"100n";;;
19;"J9";"TerminalBlock_Phoenix_PTSM-0,5-2-HV-2.5-SMD_1x02-1MP_P2.50mm_Vertical";1;"BATT_CONNECTOR";;;
20;"C21";"C_0603_1608Metric";1;"4.7u";;;
21;"R3";"R_0402_1005Metric";1;"16K";;;
22;"D15,D16";"SOT-23";2;"SP0502BAHT";;;
23;"D26";"LED_0603_1608Metric";1;"LED_net";;;
24;"BAT-1";"TestPoint_Loop_D2.50mm_Drill1.85mm";1;"BAT-";;;
25;"SW2,SW3";"SMT_4.2X3.2_";2;"SW_Push";;;
26;"C69,C71";"C_0402_1005Metric";2;"33p";;;
27;"C26";"C_0402_1005Metric_Pad0.74x0.62mm_HandSolder";1;"10n";;;
28;"R24";"R_0603_1608Metric";1;"1K";;;
29;"R89,R90,R88";"R_0402_1005Metric";3;"22R";;;
30;"C28,C25";"C_0402_1005Metric_Pad0.74x0.62mm_HandSolder";2;"4.7u";;;
31;"C6,C5";"C_0402_1005Metric";2;"0.1u";;;
32;"U2";"SOT-23-6";1;"MT3608";;;
33;"C4,C68";"C_0402_1005Metric";2;"10u";;;
34;"D23";"LED_0603_1608Metric";1;"PWR";;;
35;"R25";"R_0603_1608Metric";1;"10K";;;
36;"TP19";"TestPoint_Pad_D1.5mm";1;"THERM-";;;
37;"L3";"L_0603_1608Metric";1;"2A_bead";;;
38;"R58";"R_0402_1005Metric";1;"30.9K";;;
39;"C52";"C_0402_1005Metric";1;"100nF";;;
40;"R98,R97,R87,R99,R14";"R_0402_1005Metric";5;"4.7k";;;
41;"D27";"LED_0603_1608Metric";1;"LED_status";;;
42;"R59,R1,R95,R96";"R_0402_1005Metric";4;"10K";;;
43;"R92,R91";"R_0402_1005Metric";2;"390R";;;
44;"R13,R12";"R_0402_1005Metric";2;"10k";;;
45;"L2";"L_Chilisin_BMRx00050512-B";1;"1uH";;;
46;"D17,D1";"D_SMA";2;"SS54";;;
47;"C58,C56";"C_0603_1608Metric";2;"22uF";;;
48;"R2";"R_0402_1005Metric";1;"120K";;;
49;"C55,C54";"C_0805_2012Metric";2;"10uF";;;
50;"R26";"R_0402_1005Metric";1;"720K";;;
51;"D25";"SOT-363_SC-70-6";1;"ESD0504F";;;
52;"TP18";"TestPoint_Pad_D1.5mm";1;"THERM+";;;
53;"C35,C31";"CP_Elec_6.3x5.4";2;"220u";;;
54;"IC2";"AS312";1;"AS312";;;
55;"Q16,Q15";"SOT-23";2;"SI2302";;;
56;"C53,C57";"C_0402_1005Metric";2;"100nF_65V";;;
57;"Q9,Q8";"SOT-223-3_TabPin2";2;"NCE6005AR";;;
58;"C75,C70";"C_0402_1005Metric";2;"22p";;;
59;"U10";"SOT-23-6";1;"TPS56339DDC";;;
60;"C32,C29,C27";"C_0402_1005Metric_Pad0.74x0.62mm_HandSolder";3;"100n";;;
61;"R31,R81";"R_0402_1005Metric";2;"5.1K";;;
62;"L1";"L_Chilisin_BMRG00101030";1;"22uH";;;
63;"R27";"R_0402_1005Metric";1;"180K";;;
64;"R86";"R_0402_1005Metric";1;"0R";;;
65;"U3";"ASAIR_AM2302_P2.54mm_Vertical";1;"AM2302";;;
66;"J3";"USB_C_Receptacle_GCT_USB4105-xx-A_16P_TopMnt_Horizontal";1;"USB_C_Receptacle_USB2.0";;;
67;"L5";"L_Chilisin_BMRx00050512-B";1;"4.7uH";;;
68;"D28";"D_SOD-123";1;"4.2v Zener";;;
69;"R57";"R_0402_1005Metric";1;"30R";;;
70;"IC3";"TPS630250RNCR";1;"TPS630250RNCR";;;
71;"BAT+1";"TestPoint_Loop_D2.50mm_Drill1.85mm";1;"BAT+";;;
72;"R82";"R_0402_1005Metric";1;"47R";;;
73;"AE4";"CONN_2337019-1_TEC";1;"GPS_ANTENNA";;;
74;"C23,C67";"CP_EIA-3528-21_Kemet-B";2;"220u";;;
75;"L9";"L_0402_1005Metric";1;"47nH";;;
76;"AE3";"CONN_2337019-1_TEC";1;"GPRS_ANTENNA";;;
77;"IC4";"SIM7600GHR2";1;"SIM7600G-H_R2";;;
